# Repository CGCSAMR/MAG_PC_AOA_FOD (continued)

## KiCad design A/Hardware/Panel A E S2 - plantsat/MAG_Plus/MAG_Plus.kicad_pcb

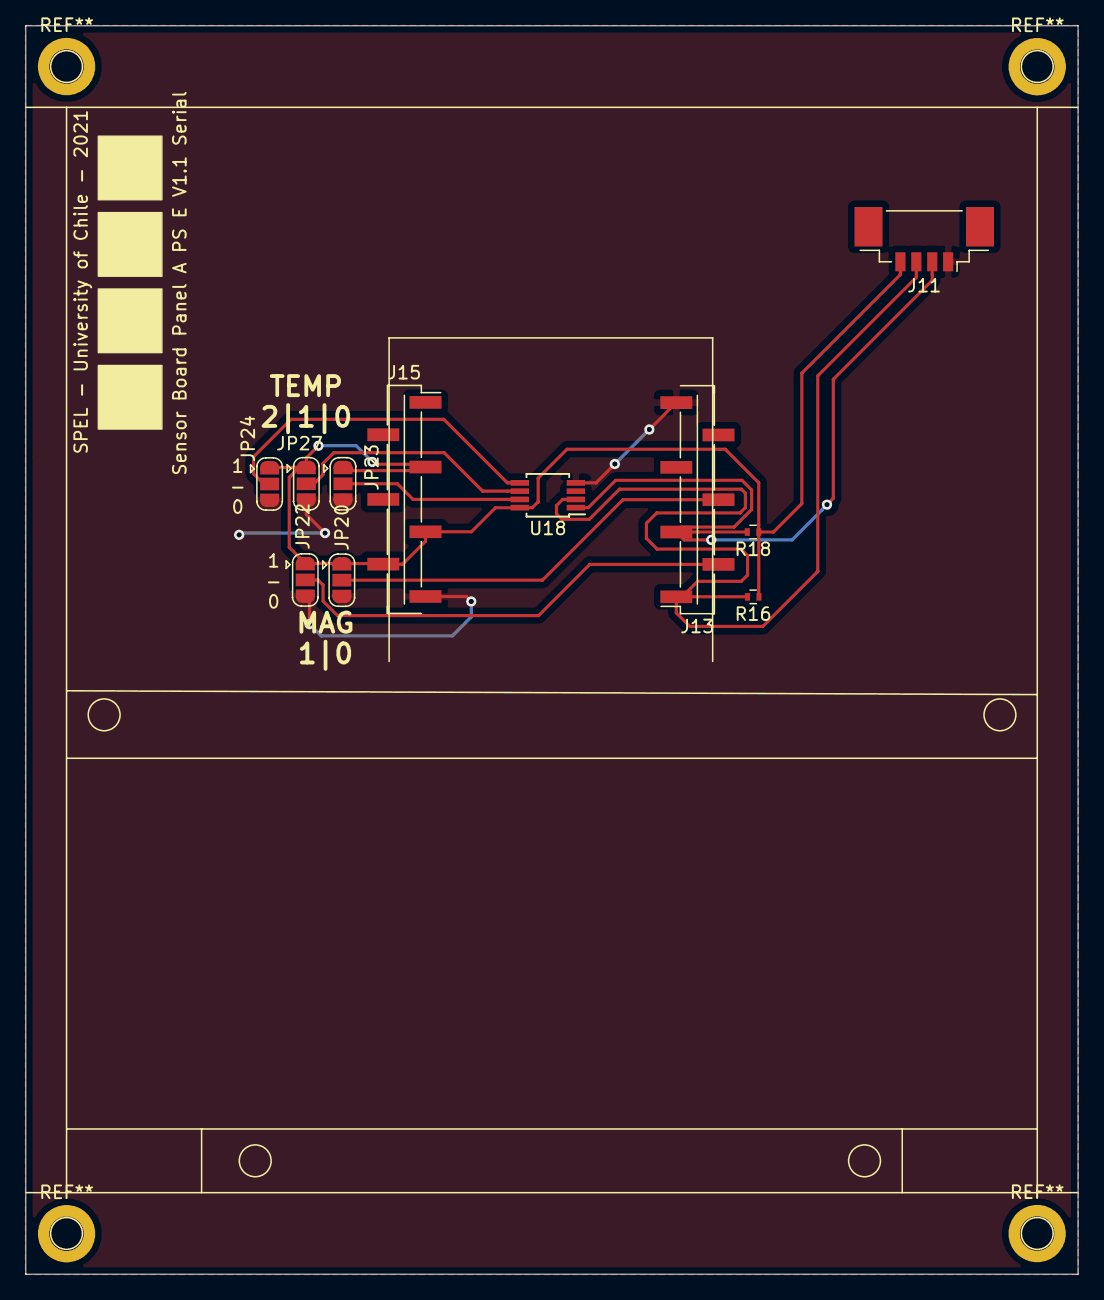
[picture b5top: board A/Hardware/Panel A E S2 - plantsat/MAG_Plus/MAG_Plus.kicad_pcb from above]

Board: 2 copper layers, 82.6 x 98.0 mm, 11 parts (0 on the bottom side), 9 nets.

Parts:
J11: Conn_01x04_Male; Molex_PicoBlade_53398-0471_04x1.25mm_Straight
J13, J15: Conn_01x07_Female; Pin_Header_Straight_1x07_Pitch2.54mm_SMD_Pin1Right
JP20, JP22, JP23, JP24, JP27: Jumper_3_Open; SolderJumper-3_P1.3mm_Open_RoundedPad1.0x1.5mm
R16, R18: R; R_0402
U18: MCP9804_MSOP; MSOP-8_3x3mm_Pitch0.65mm

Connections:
GND: J11.1, J13.7, J15.7, JP20.3, JP22.3, JP23.3, JP24.3, JP27.3, U18.4
MAG2_A0: JP23.2, U18.7
MAG2_A1: JP27.2, U18.6
MAG2_A2: JP24.2, U18.5
MAG2_BIT0: J13.4, JP20.2
MAG2_BIT1: J13.2, JP22.2
MAG_3V3: J11.4, J15.3, J15.5, J15.6, JP20.1, JP22.1, JP23.1, JP24.1, JP27.1, R16.1, R18.1, U18.8
RPI_SCL: J11.3, J13.1, R16.2, U18.2
RPI_SDA: J11.2, J13.3, R18.2, U18.1

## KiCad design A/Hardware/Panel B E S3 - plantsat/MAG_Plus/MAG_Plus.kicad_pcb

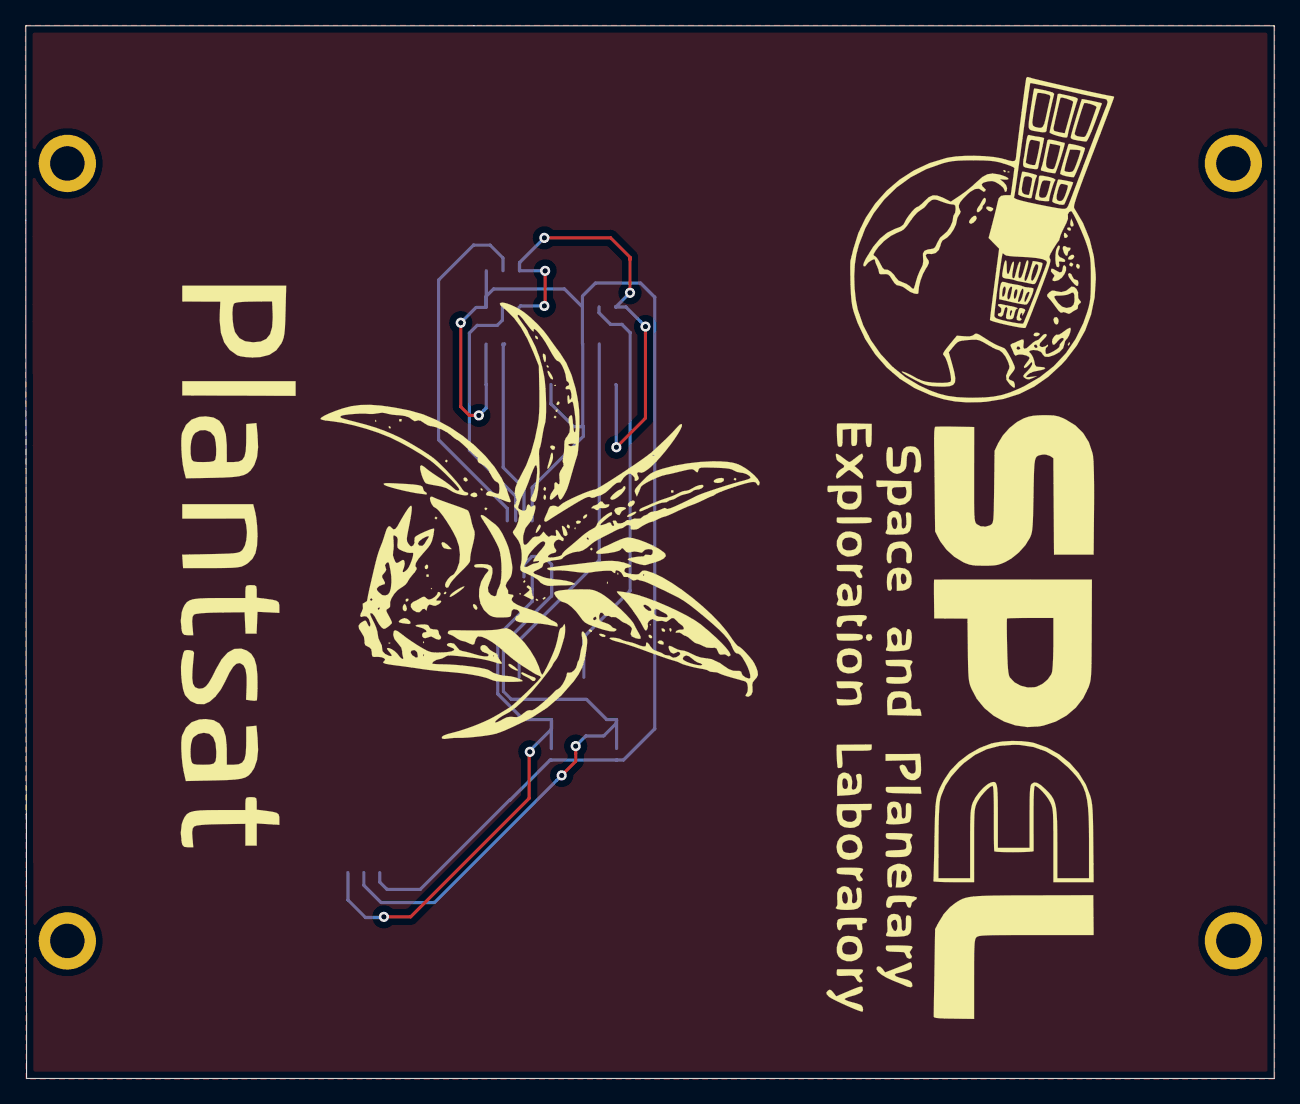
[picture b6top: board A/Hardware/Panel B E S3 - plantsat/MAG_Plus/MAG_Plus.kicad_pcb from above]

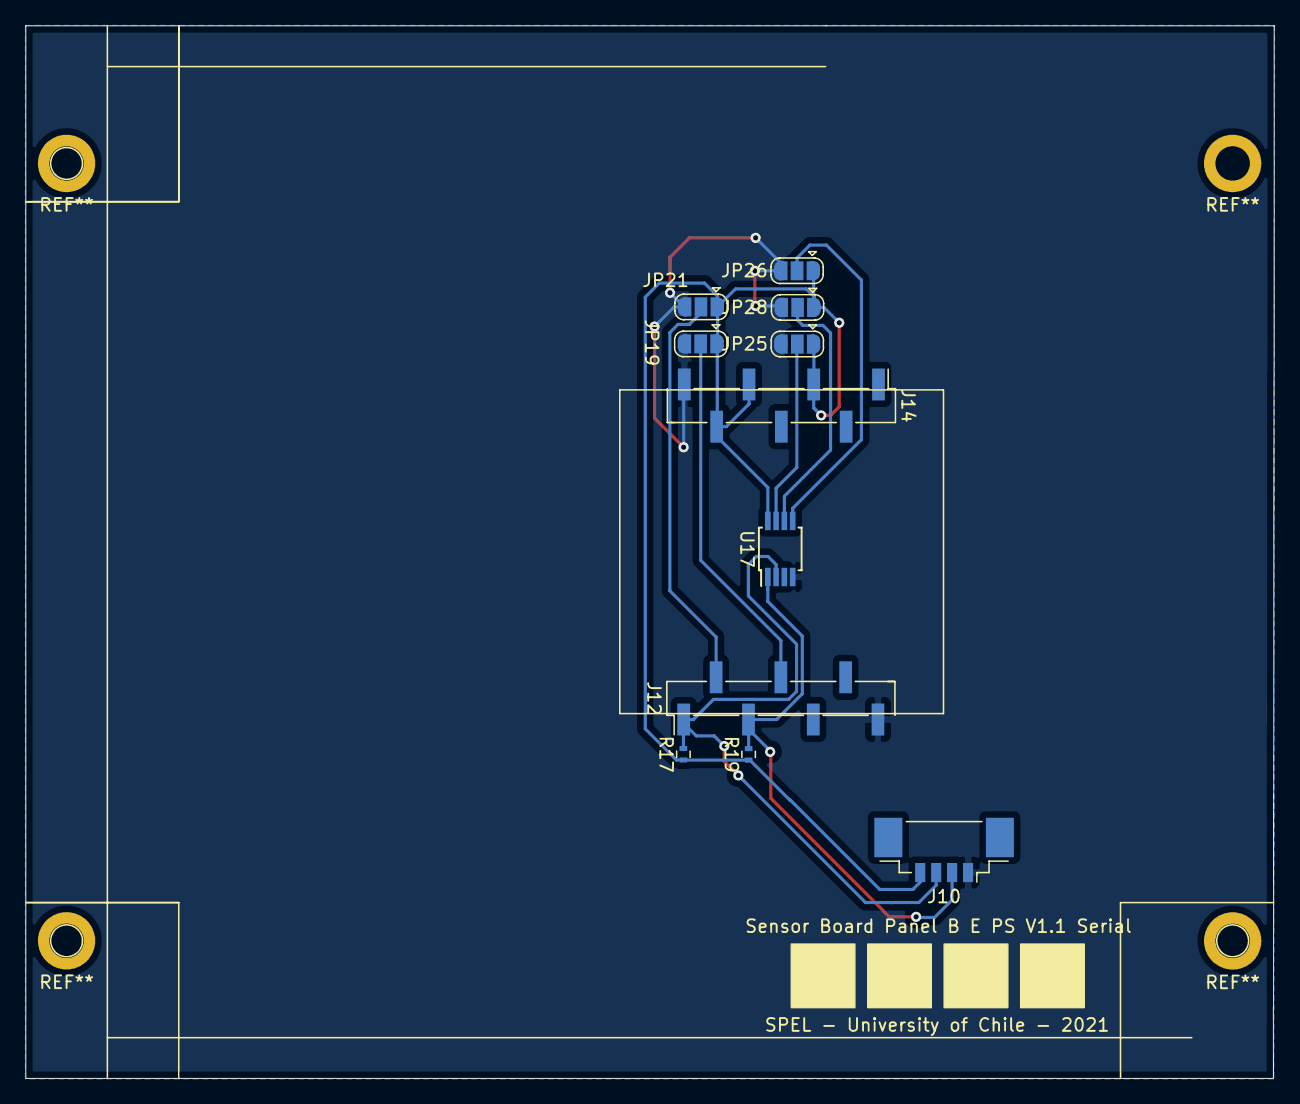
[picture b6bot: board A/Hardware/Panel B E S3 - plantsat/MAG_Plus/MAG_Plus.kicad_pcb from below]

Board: 2 copper layers, 98.0 x 82.6 mm, 11 parts (11 on the bottom side), 9 nets.

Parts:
J10: Conn_01x04_Male; Molex_PicoBlade_53398-0471_04x1.25mm_Straight
J12, J14: Conn_01x07_Female; Pin_Header_Straight_1x07_Pitch2.54mm_SMD_Pin1Left
JP19, JP21, JP25, JP26, JP28: Jumper_3_Open; SolderJumper-3_P1.3mm_Open_RoundedPad1.0x1.5mm
R17, R19: R; R_0402
U17: MCP9804_MSOP; MSOP-8_3x3mm_Pitch0.65mm

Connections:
GND: J10.1, J12.7, J14.7, JP19.3, JP21.3, JP25.3, JP26.3, JP28.3, U17.4
MAG1_A0: JP25.2, U17.7
MAG1_A1: JP28.2, U17.6
MAG1_A2: JP26.2, U17.5
MAG1_BIT0: J12.4, JP19.2
MAG1_BIT1: J12.2, JP21.2
MAG_3V3: J10.4, J14.3, J14.5, J14.6, JP19.1, JP21.1, JP25.1, JP26.1, JP28.1, R17.1, R19.1, U17.8
RPI_SCL: J10.3, J12.1, R17.2, U17.2
RPI_SDA: J10.2, J12.3, R19.2, U17.1

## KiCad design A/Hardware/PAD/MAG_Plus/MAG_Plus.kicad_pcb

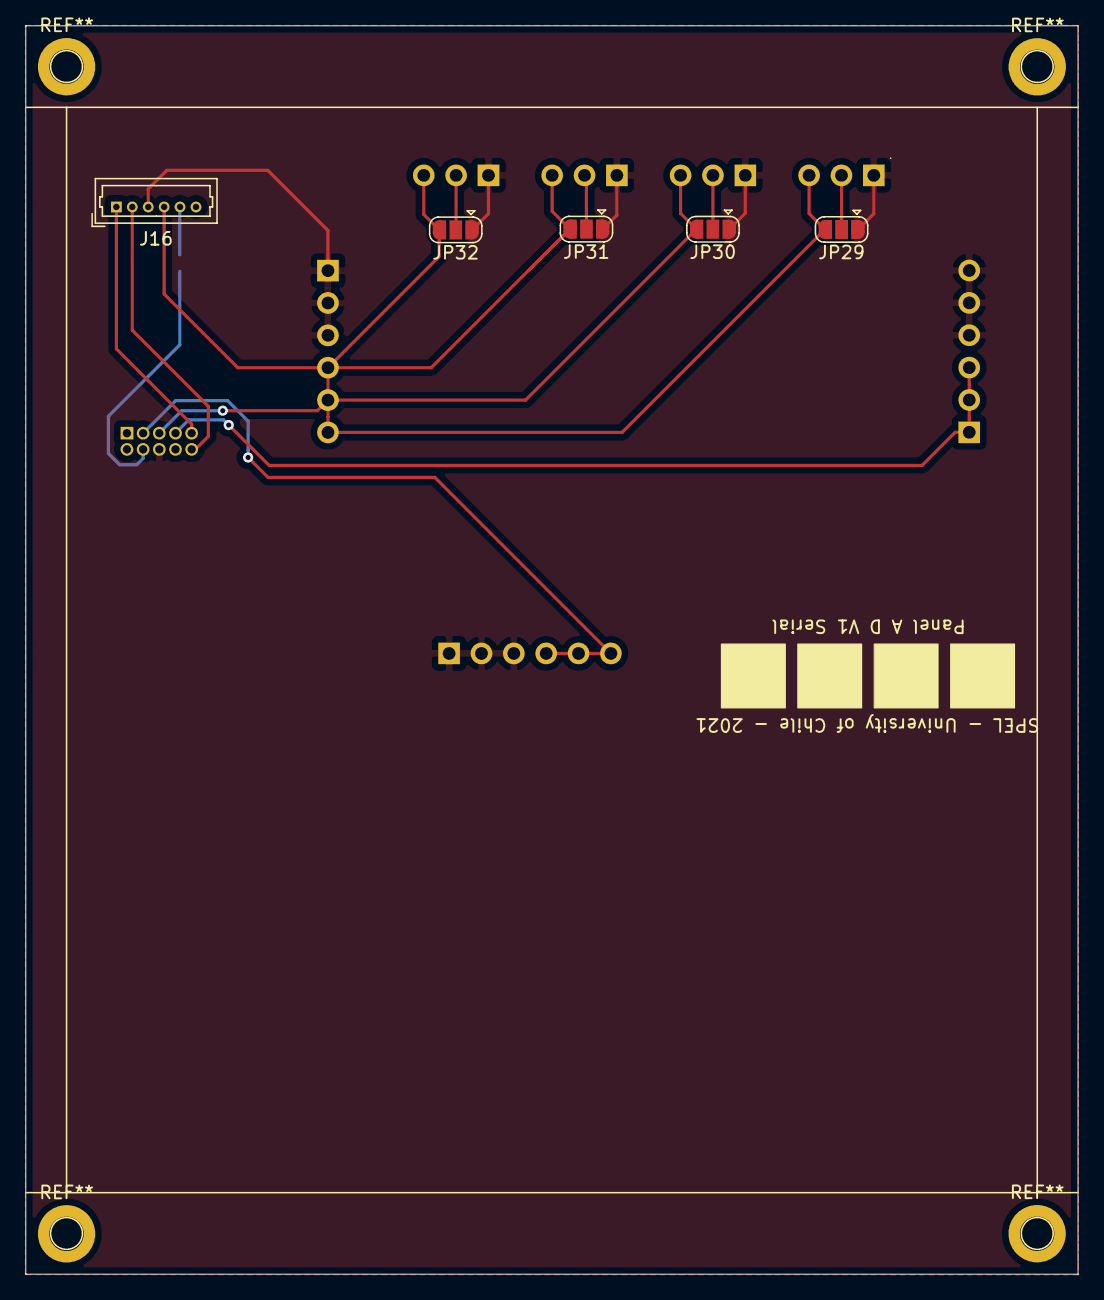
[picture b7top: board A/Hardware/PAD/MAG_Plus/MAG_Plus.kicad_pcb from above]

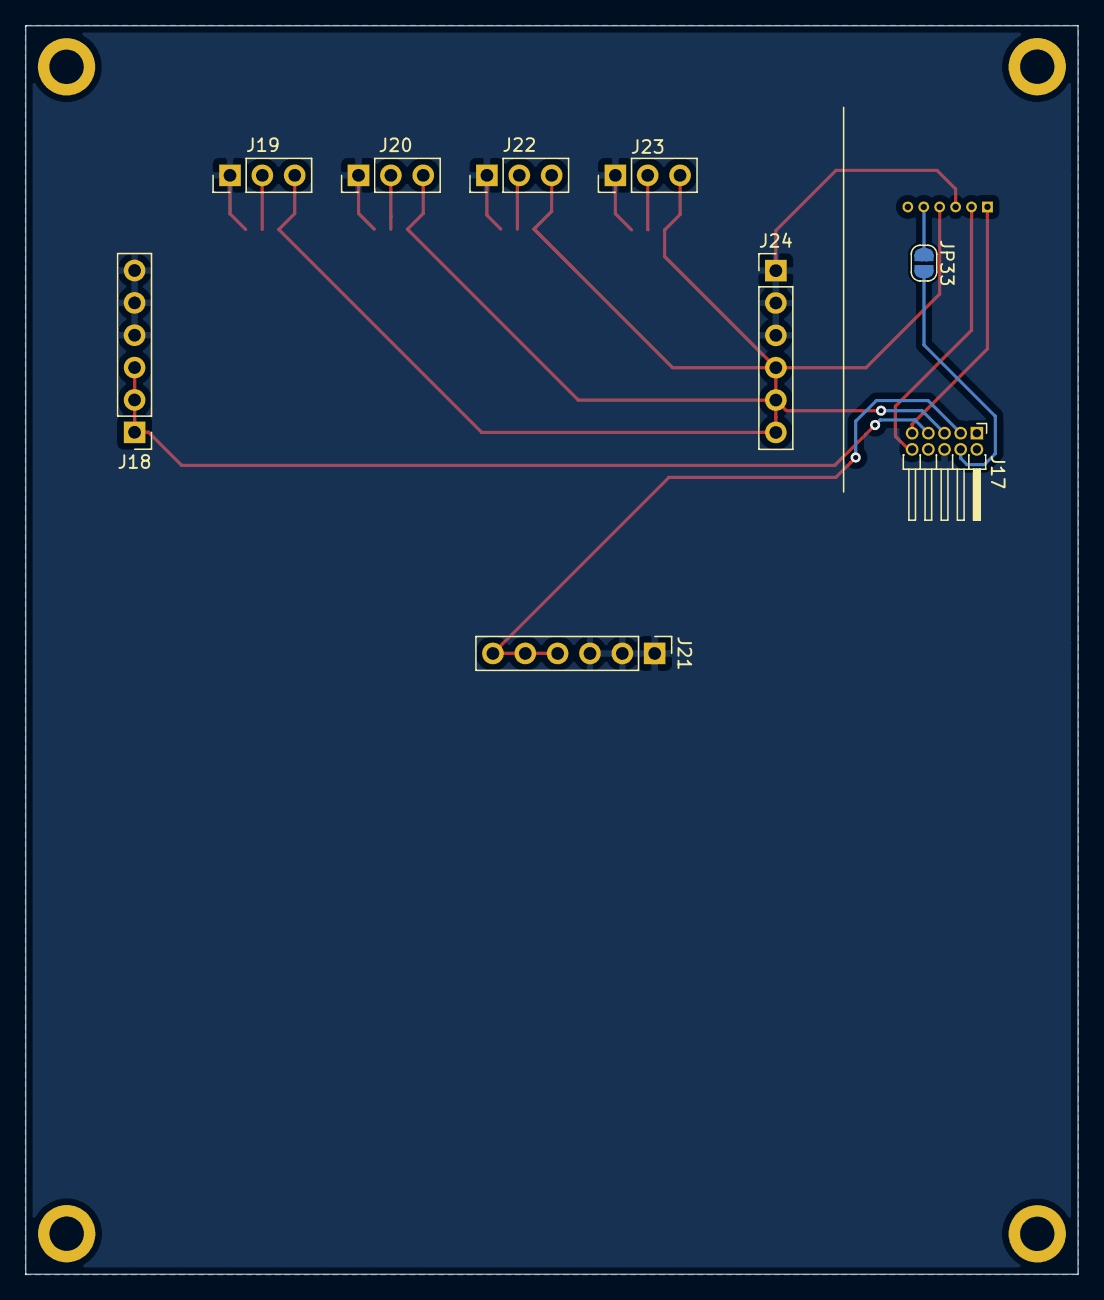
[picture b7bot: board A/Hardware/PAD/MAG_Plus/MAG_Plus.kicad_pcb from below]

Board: 2 copper layers, 82.6 x 98.0 mm, 14 parts (9 on the bottom side), 12 nets.

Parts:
J16: Conn_01x06_Male; Molex_PicoBlade_53047-0610_06x1.25mm_Straight
J17: Conn_02x05_Counter_Clockwise; Pin_Header_Angled_2x05_Pitch1.27mm
J18, J21, J24: Conn_01x06_Male; Pin_Header_Straight_1x06_Pitch2.54mm
J19, J20, J22, J23: Conn_01x03_Male; Pin_Header_Straight_1x03_Pitch2.54mm
JP29, JP30, JP31, JP32: Jumper_3_Open; SolderJumper-3_P1.3mm_Open_RoundedPad1.0x1.5mm
JP33: Jumper_2_Open; SolderJumper-2_P1.3mm_Open_RoundedPad1.0x1.5mm

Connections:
ENN: J20.2, JP30.2
ENP: J23.2, JP32.2
GND: J16.3, J17.6, J18.4, J18.5, J18.6, J19.1, J20.1, J21.1, J21.2, J21.3, J22.1, J23.1, J24.1, J24.2, J24.3, JP29.1, JP30.1, JP31.1, JP32.1
LPS_3V3: J16.5, JP33.1
LPS_3V3J: J17.4, JP33.2
LPS_5V: J16.4, J17.5, J19.3, J20.3, J22.3, J23.3, J24.4, J24.5, J24.6, JP29.3, JP30.3, JP31.3, JP32.3
LPS_RX: J16.1, J17.9
LPS_TX: J16.2, J17.10
PSN: J19.2, JP29.2
PSP: J22.2, JP31.2
VNEG: J17.7, J18.1, J18.2, J18.3
VPOS: J17.3, J21.4, J21.5, J21.6

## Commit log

2021-08-12 Images
2021-08-12 Change Sheets by Schematic
2021-08-13 Update PCB A
2021-08-14 new modifications pcb
2021-08-16 More PCB Changes
2021-08-20 PCB update
2021-08-20 add langmuir probe
2021-11-10 Update PCBs
    New version of PCBs
2021-11-23 More changes
2022-08-22 minor changes
